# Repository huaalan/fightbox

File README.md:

# Fightbox
All button fightbox with 11 buttons

# Firmware
Use https://gp2040-ce.info/ to flash firmware
1. Download firmware. It is recommended to get the one for flatbox 5.
2. Flash the firmware, connect the board to a computer with a USB cable, then press the RESET button while holding the BOOT button on the RP2040-Zero. A drive named "RPI-RP2" should appear. Copy the UF2 file you downloaded to that drive.
3. Now that firmware has been flashed, use the built in web configurator to map buttons and configure controller (instructions at gp2040-ce.info)

# Troubleshooting
Start button bind missing?
If you used a firmware other than flatbox 5, try using the flatbox 5 since the pinouts for other firmware could be different.

Missing start button to get into web config after rebinding.
If you can't get the start bind back from flashing firmware, you will want to do a nuke flash and reflash the flatbox firmware so you will have the default buttons. The nuke flash will wipe all configurations.

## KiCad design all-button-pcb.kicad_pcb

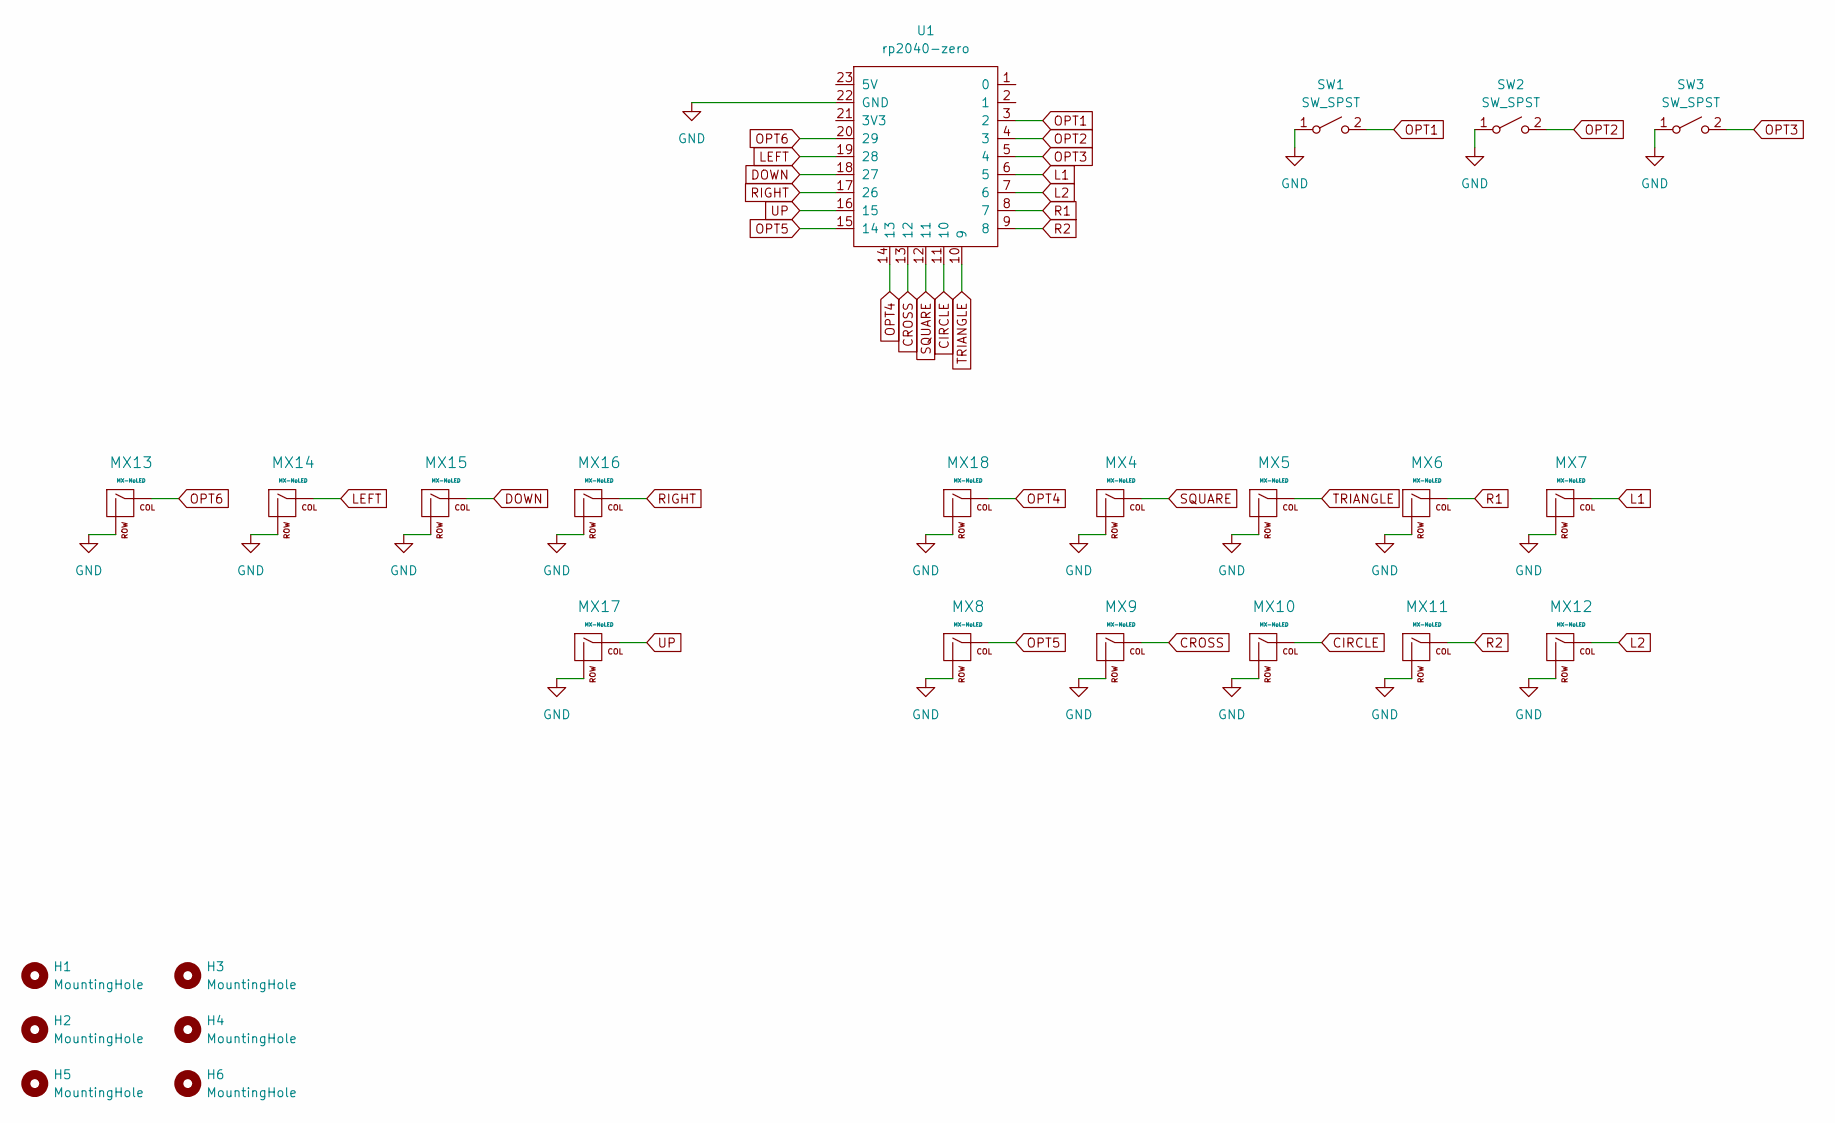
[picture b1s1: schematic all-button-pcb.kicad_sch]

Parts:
H1, H2, H3, H4, H5, H6: MountingHole; MountingHole_6.5mm
MX4, MX5, MX6, MX7, MX8, MX9, MX10, MX11, MX12, MX13, MX14, MX15, MX16, MX18: MX-NoLED; MX-Hotswap-1U-24mm
MX17: MX-NoLED; MX-Hotswap-1U-30mm
SW1, SW2, SW3: SW_SPST; SW_PUSH_6mm_H13mm
U1: rp2040-zero; RP2040-Zero

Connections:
CIRCLE: MX10.1 (COL), U1.11 (10)
CROSS: MX9.1 (COL), U1.13 (12)
DOWN: MX15.1 (COL), U1.18 (27)
GND: MX4.2 (ROW), MX5.2 (ROW), MX6.2 (ROW), MX7.2 (ROW), MX8.2 (ROW), MX9.2 (ROW), MX10.2 (ROW), MX11.2 (ROW), MX12.2 (ROW), MX13.2 (ROW), MX14.2 (ROW), MX15.2 (ROW), MX16.2 (ROW), MX17.2 (ROW), MX18.2 (ROW), SW1.1 (A), SW2.1 (A), SW3.1 (A), U1.22 (GND)
L1: MX7.1 (COL), U1.6 (5)
L2: MX12.1 (COL), U1.7 (6)
LEFT: MX14.1 (COL), U1.19 (28)
OPT1: SW1.2 (B), U1.3 (2)
OPT2: SW2.2 (B), U1.4 (3)
OPT3: SW3.2 (B), U1.5 (4)
OPT4: MX18.1 (COL), U1.14 (13)
OPT5: MX8.1 (COL), U1.15 (14)
OPT6: MX13.1 (COL), U1.20 (29)
R1: MX6.1 (COL), U1.8 (7)
R2: MX11.1 (COL), U1.9 (8)
RIGHT: MX16.1 (COL), U1.17 (26)
SQUARE: MX4.1 (COL), U1.12 (11)
TRIANGLE: MX5.1 (COL), U1.10 (9)
UP: MX17.1 (COL), U1.16 (15)

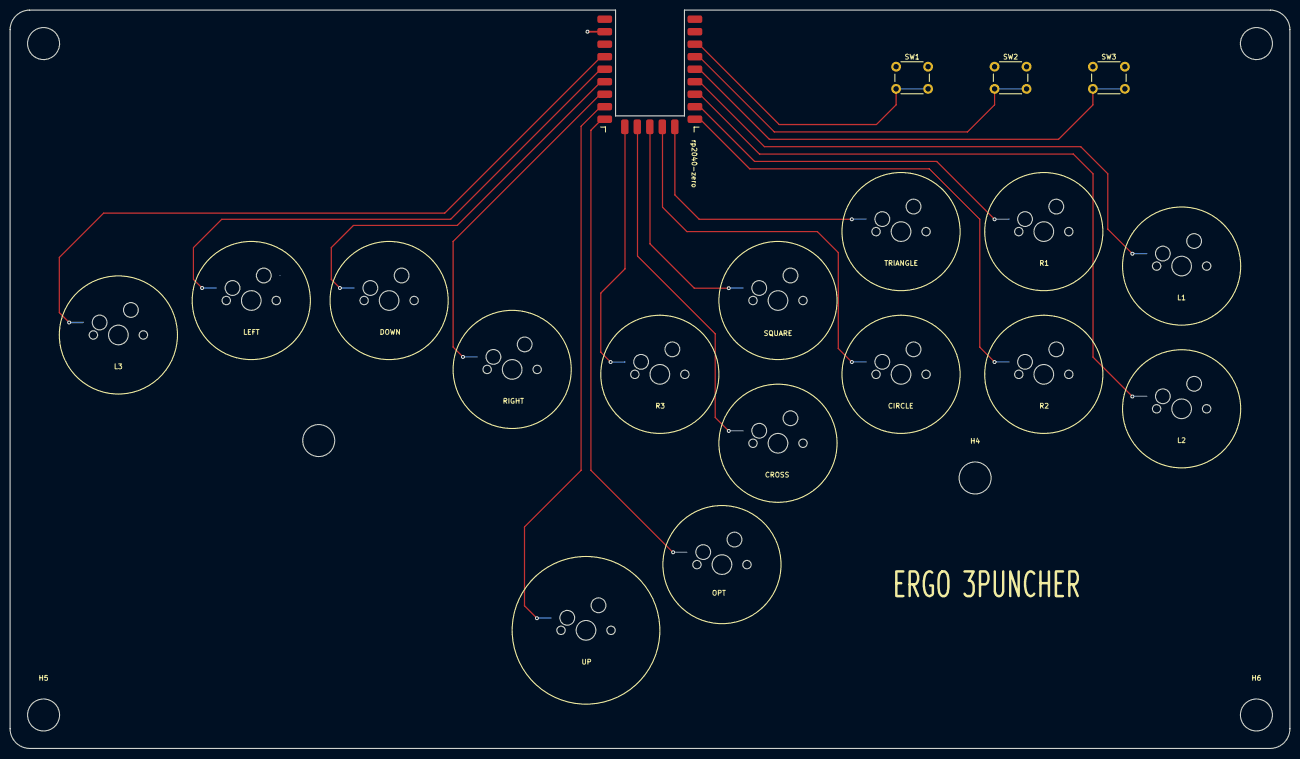
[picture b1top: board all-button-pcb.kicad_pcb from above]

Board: 2 copper layers, 260.0 x 150.0 mm, 25 parts (0 on the bottom side), 19 nets.

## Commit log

2023-08-13 init
    initial files generated
2023-08-13 add submodules
    submodule footprint libraries for mx switches and other keyboard parts
2023-08-13 add footprint libraries
2023-08-14 add mcu library
    add symbol and footprint for rp2040 zero
2023-08-20 base design
    base design of schematics and pcb
2023-08-31 fix gnd pad placement
    gnd pad placement swap between 22 and 23
2023-11-08 Update README.md
    simple firmware installation instructions
2023-11-14 supportive holes
    added supportive holes for corners to trim case
2023-11-15 kicad 3d case export
    added 3d case export from kicad
2023-11-15 imported pcb model
2023-12-07 initial blender model
    3d blender model for case. Still need to complete bottom plate
2023-12-07 Update README.md
    updated description for pcb changes.
